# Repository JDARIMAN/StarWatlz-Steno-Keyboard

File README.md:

# StarWatlz-Steno-Keyboard
## STARDANCE HACKPAD PROJECT BASED ON STARBOARD AND POLYGOT STENO KEYBOARDS

An attempt at making a hybrid QWERTY and Stenography keyboard with a build in LCD and Volume Knob using a rotary encoder.

LCD displays Volume, mode, as well as wpm, since Stenography is meant to be fast

Here's the PCB:

Yes There is a ground plate 

Schematic:

This board uses low profile switches as it is standard on steno keyboards

# AI USAGE DECLARATION
Even if I haven't written any firmware, as I don't have my microcontroller yet, it will be AI assisted. Most of the AI usage comes down to the tolerances of the designs measurements.

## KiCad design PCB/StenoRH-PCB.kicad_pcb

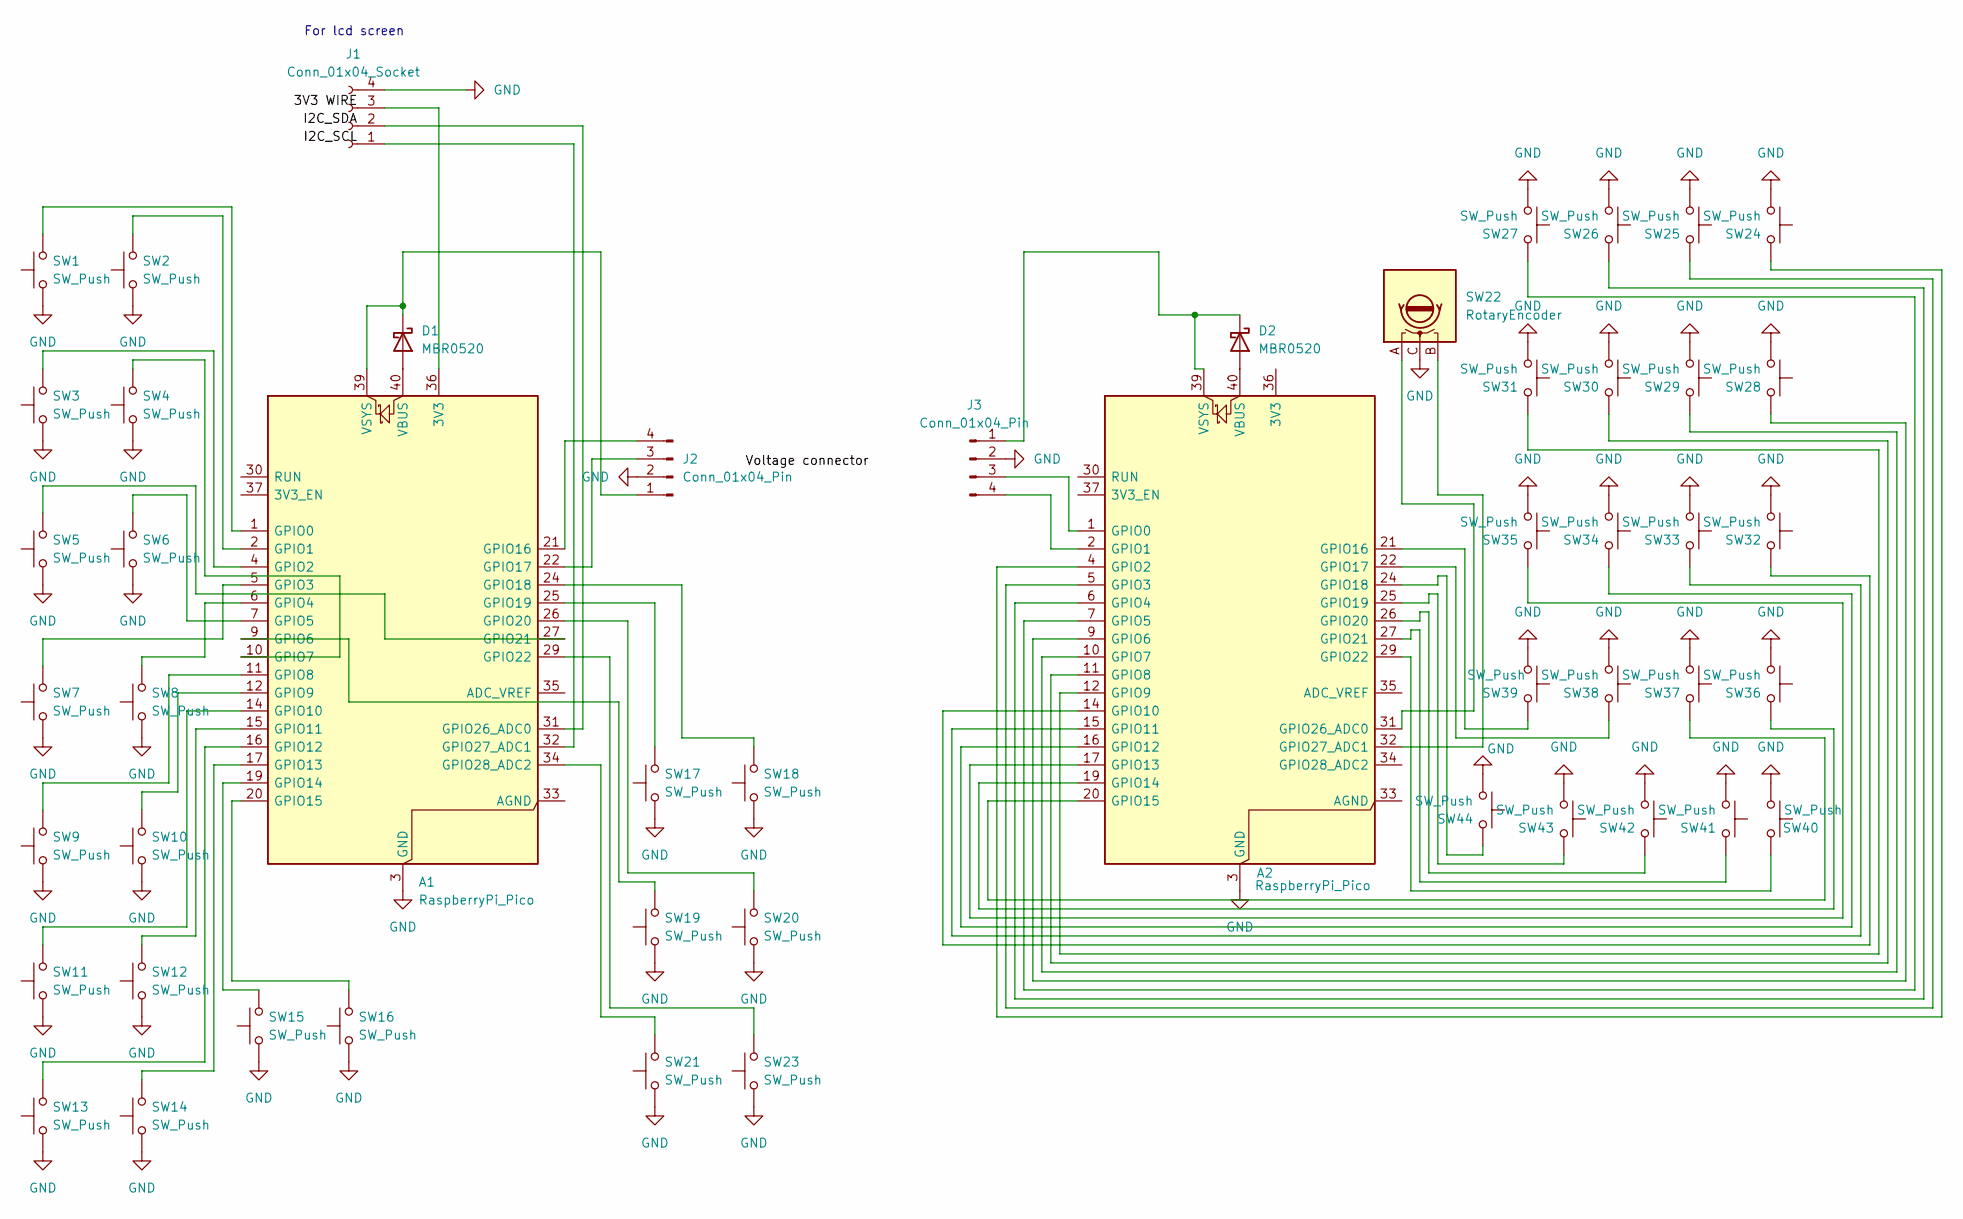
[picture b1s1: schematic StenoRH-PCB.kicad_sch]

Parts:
A1, A2: RaspberryPi_Pico; RaspberryPi_Pico_Common_Unspecified
D1, D2: MBR0520; D_SOD-123
J1: Conn_01x04_Socket; PinSocket_1x04_P2.54mm_Horizontal
J2, J3: Conn_01x04_Pin; PinHeader_1x04_P2.54mm_Horizontal
SW1, SW2, SW3, SW4, SW5, SW6, SW7, SW8, SW9, SW10, SW11, SW12, SW13, SW14, SW15, SW16, SW17, SW18, SW19, SW20, SW21, SW23, SW24, SW25, SW26, SW27, SW28, SW29, SW30, SW31, SW32, SW33, SW34, SW35, SW36, SW37, SW38, SW39, SW40, SW41, SW42, SW43, SW44: SW_Push; SW_Hotswap_Kailh_Choc_V1
SW22: RotaryEncoder; RotaryEncoder_Alps_EC11E-Switch_Vertical_H20mm_MountingHoles

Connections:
GND: A1.3 (GND), A1.8 (GND), A1.13 (GND), A1.18 (GND), A1.23 (GND), A1.28 (GND), A1.38 (GND), A2.3 (GND), A2.8 (GND), A2.13 (GND), A2.18 (GND), A2.23 (GND), A2.28 (GND), A2.38 (GND), J1.4, J2.2, J3.2, SW1.1, SW2.1, SW3.1, SW4.1, SW5.1, SW6.1, SW7.1, SW8.1, SW9.1, SW10.1, SW11.1, SW12.1, SW13.1, SW14.1, SW15.1, SW16.1, SW17.1, SW18.1, SW19.1, SW20.1, SW21.1, SW22.C, SW23.1, SW24.1, SW25.1, SW26.1, SW27.1, SW28.1, SW29.1, SW30.1, SW31.1, SW32.1, SW33.1, SW34.1, SW35.1, SW36.1, SW37.1, SW38.1, SW39.1, SW40.1, SW41.1, SW42.1, SW43.1, SW44.1
unnamed: A1.36 (3V3), J1.3
unnamed: A1.1 (GPIO0), SW1.2
unnamed: A1.2 (GPIO1), SW2.2
unnamed: A1.4 (GPIO2), SW3.2
unnamed: A1.5 (GPIO3), SW7.2
unnamed: A1.6 (GPIO4), SW8.2
unnamed: A1.7 (GPIO5), SW6.2
unnamed: A1.9 (GPIO6), SW19.2
unnamed: A1.10 (GPIO7), SW4.2
unnamed: A1.11 (GPIO8), SW9.2
unnamed: A1.12 (GPIO9), SW10.2
unnamed: A1.14 (GPIO10), SW11.2
unnamed: A1.15 (GPIO11), SW12.2
unnamed: A1.16 (GPIO12), SW13.2
unnamed: A1.17 (GPIO13), SW14.2
unnamed: A1.19 (GPIO14), SW15.2
unnamed: A1.20 (GPIO15), SW16.2
unnamed: A1.21 (GPIO16), J2.4
unnamed: A1.22 (GPIO17), J2.3
unnamed: A1.24 (GPIO18), SW18.2
unnamed: A1.25 (GPIO19), SW17.2
unnamed: A1.26 (GPIO20), SW20.2
unnamed: A1.27 (GPIO21), SW5.2
unnamed: A1.29 (GPIO22), SW23.2
unnamed: A1.31 (GPIO26_ADC0), J1.2
unnamed: A1.32 (GPIO27_ADC1), J1.1
unnamed: A1.34 (GPIO28_ADC2), SW21.2
unnamed: A1.40 (VBUS), D1.2 (A)
unnamed: A1.39 (VSYS), D1.1 (K), J2.1
unnamed: A2.1 (GPIO0), J3.3
unnamed: A2.2 (GPIO1), J3.4
unnamed: A2.4 (GPIO2), SW24.2
unnamed: A2.5 (GPIO3), SW25.2
unnamed: A2.6 (GPIO4), SW26.2
unnamed: A2.7 (GPIO5), SW27.2
unnamed: A2.9 (GPIO6), SW28.2
unnamed: A2.10 (GPIO7), SW29.2
unnamed: A2.11 (GPIO8), SW30.2
unnamed: A2.12 (GPIO9), SW31.2
unnamed: A2.14 (GPIO10), SW32.2
unnamed: A2.15 (GPIO11), SW33.2
unnamed: A2.16 (GPIO12), SW34.2
unnamed: A2.17 (GPIO13), SW35.2
unnamed: A2.19 (GPIO14), SW36.2
unnamed: A2.20 (GPIO15), SW37.2
unnamed: A2.21 (GPIO16), SW39.2
unnamed: A2.22 (GPIO17), SW38.2
unnamed: A2.24 (GPIO18), SW44.2
unnamed: A2.25 (GPIO19), SW43.2
unnamed: A2.26 (GPIO20), SW42.2
unnamed: A2.27 (GPIO21), SW41.2
unnamed: A2.29 (GPIO22), SW40.2
unnamed: A2.31 (GPIO26_ADC0), SW22.A
unnamed: A2.32 (GPIO27_ADC1), SW22.B
unnamed: A2.40 (VBUS), D2.2 (A)
unnamed: A2.39 (VSYS), D2.1 (K), J3.1

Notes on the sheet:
For lcd screen

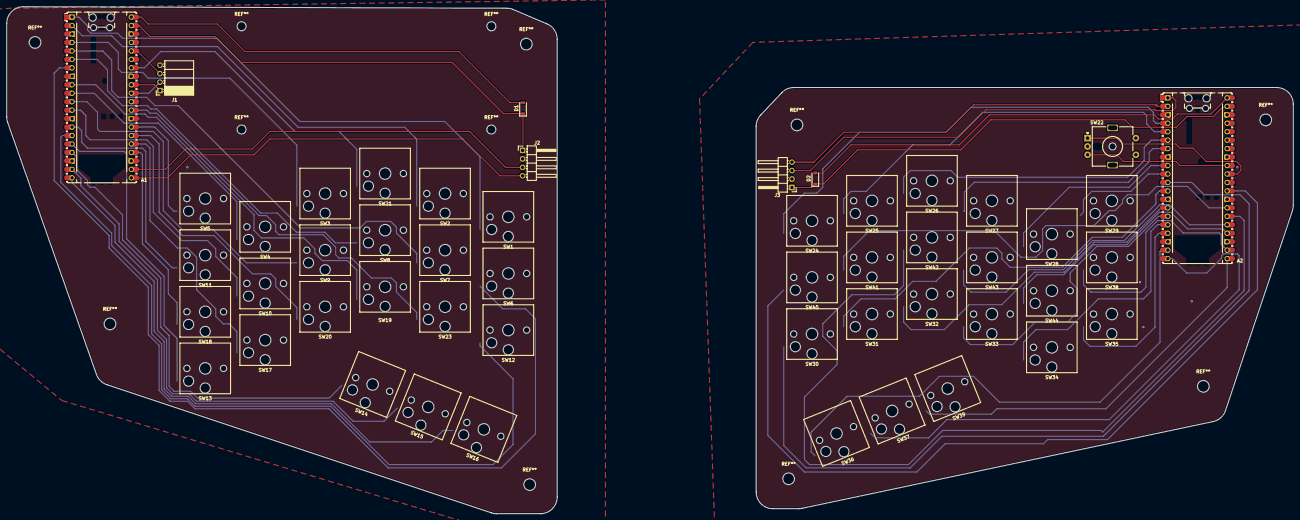
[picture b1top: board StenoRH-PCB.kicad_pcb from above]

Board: 2 copper layers, 386.2 x 152.2 mm, 51 parts (0 on the bottom side), 57 nets.
